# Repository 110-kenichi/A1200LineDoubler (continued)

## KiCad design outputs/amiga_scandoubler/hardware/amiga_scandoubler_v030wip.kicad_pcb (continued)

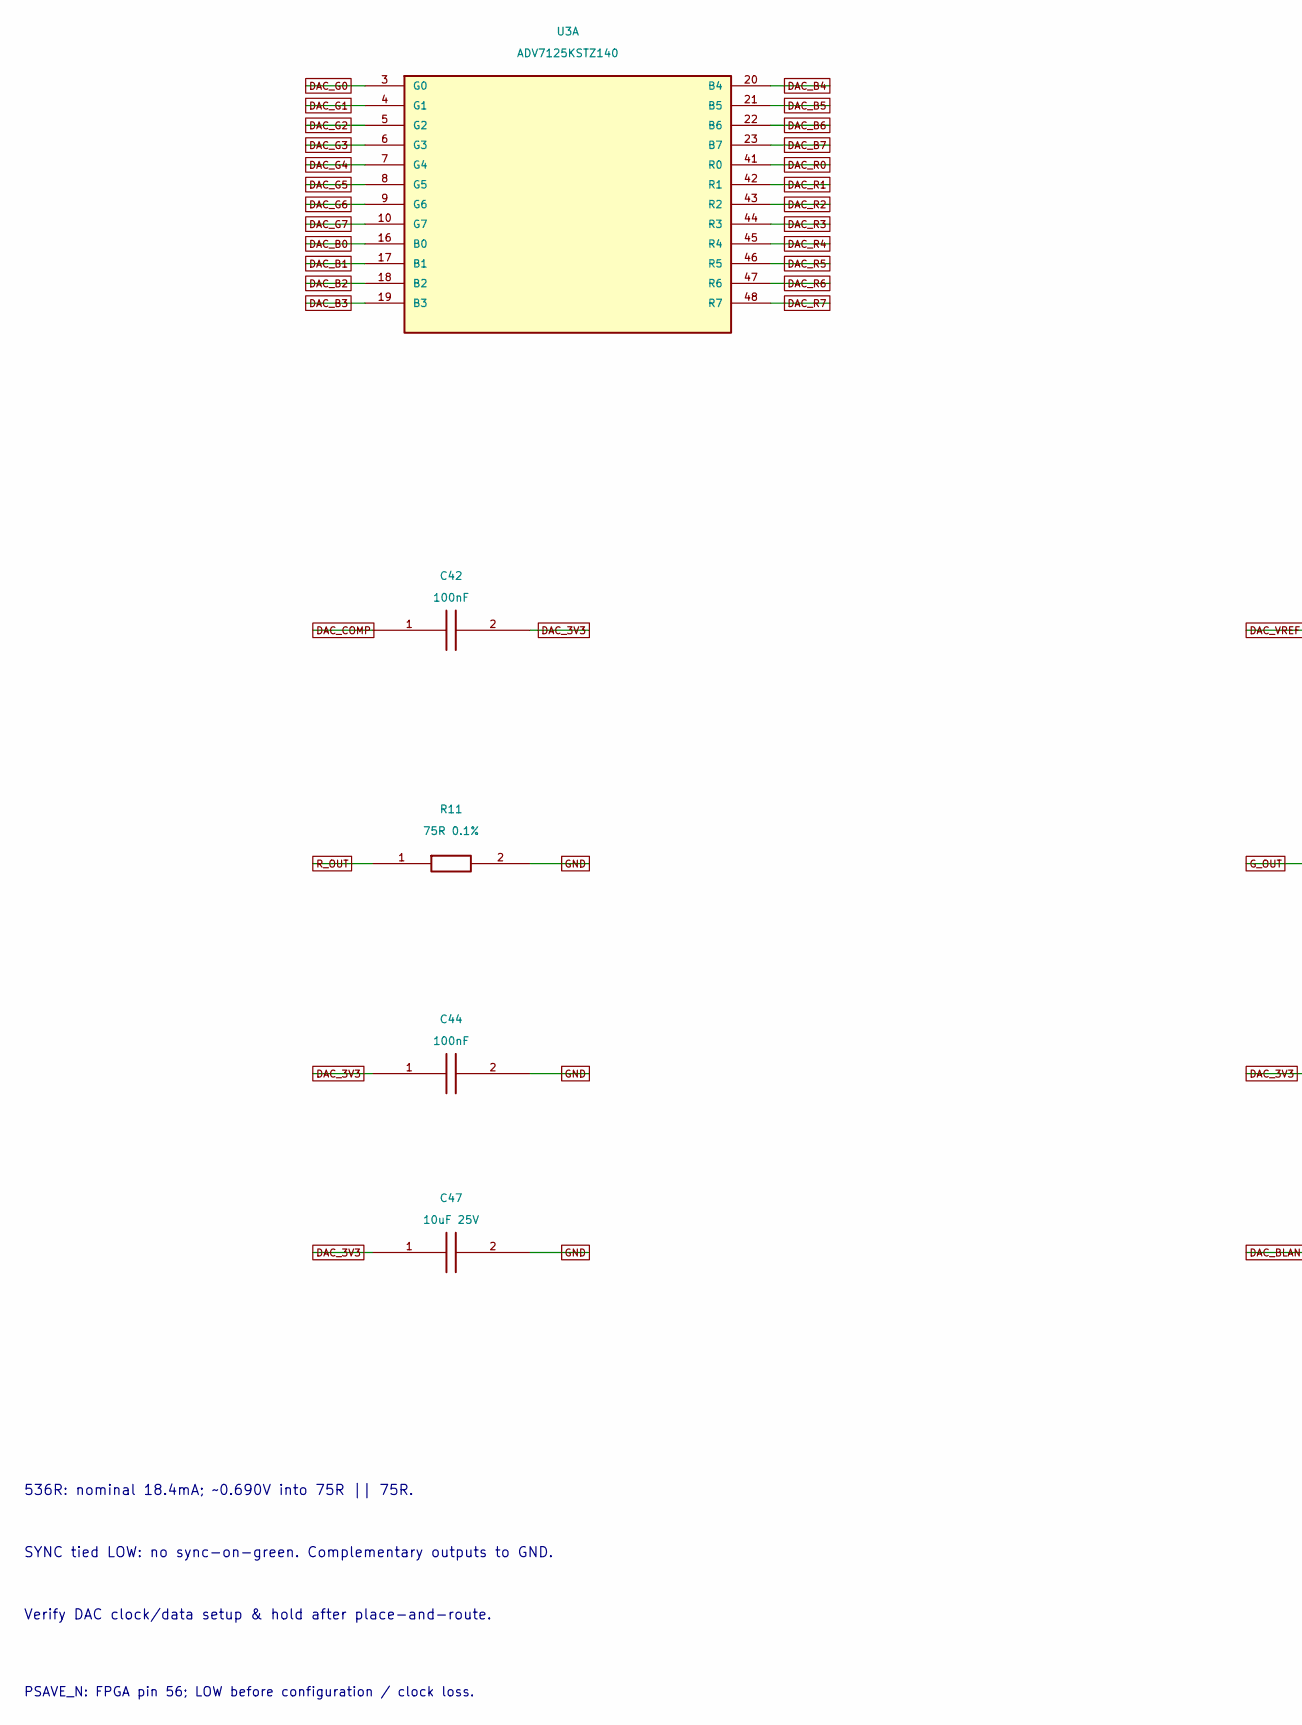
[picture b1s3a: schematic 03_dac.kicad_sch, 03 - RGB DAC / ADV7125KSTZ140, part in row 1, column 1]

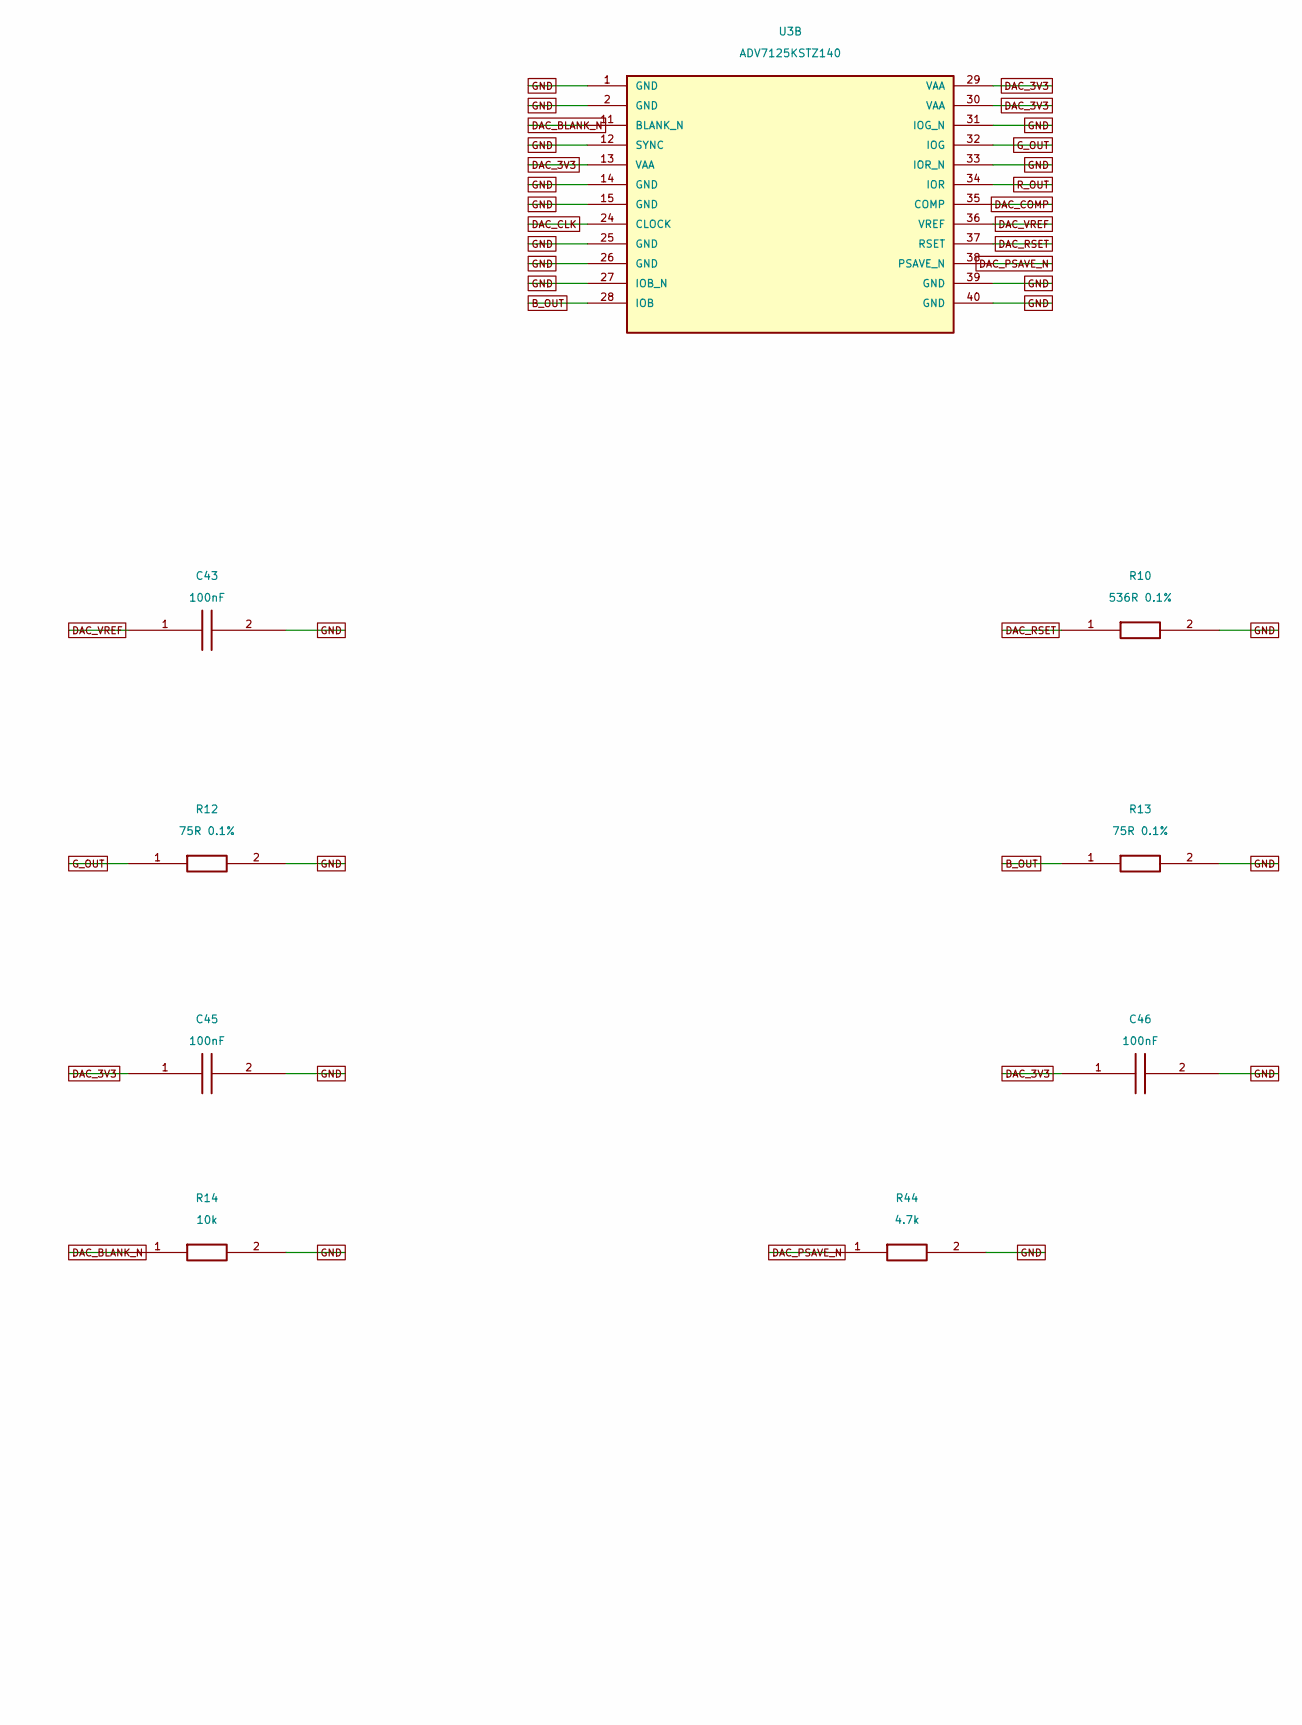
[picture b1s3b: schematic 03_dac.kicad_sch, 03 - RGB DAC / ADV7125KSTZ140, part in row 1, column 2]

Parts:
C42: 100nF; C_0402_1005Metric; MPN CL05B104KO5NNNC; LCSC C1525
C43, C44, C45, C46: 100nF; C_0603_1608Metric; MPN CC0603KRX7R9BB104; LCSC C14663
C47: 10uF 25V; C_0805_2012Metric; MPN CL21A106KAYNNNE; LCSC C15850
R10: 536R 0.1%; R_0603_1608Metric; MPN RT0603BRD07536RL; LCSC C861466
R11, R12, R13: 75R 0.1%; R_0603_1608Metric; MPN AR03BTCX0750; LCSC C319466
R14: 10k; R_0603_1608Metric; MPN 0603WAF1002T5E; LCSC C25804
R44: 4.7k; R_0603_1608Metric; MPN 0603WAF4701T5E; LCSC C23162
U3: ADV7125KSTZ140; LQFP-48_7x7mm_P0.5mm; MPN ADV7125KSTZ140; LCSC C9668

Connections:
B_OUT: R13.1, U3.28 (IOB); also elsewhere on the board
DAC_3V3: C42.2, C44.1, C45.1, C46.1, C47.1, U3.13 (VAA), U3.29 (VAA), U3.30 (VAA); also elsewhere on the board
DAC_B0: U3.16 (B0); also elsewhere on the board
DAC_B1: U3.17 (B1); also elsewhere on the board
DAC_B2: U3.18 (B2); also elsewhere on the board
DAC_B3: U3.19 (B3); also elsewhere on the board
DAC_B4: U3.20 (B4); also elsewhere on the board
DAC_B5: U3.21 (B5); also elsewhere on the board
DAC_B6: U3.22 (B6); also elsewhere on the board
DAC_B7: U3.23 (B7); also elsewhere on the board
DAC_BLANK_N: R14.1, U3.11 (BLANK_N); also elsewhere on the board
DAC_CLK: U3.24 (CLOCK); also elsewhere on the board
DAC_COMP: C42.1, U3.35 (COMP)
DAC_G0: U3.3 (G0); also elsewhere on the board
DAC_G1: U3.4 (G1); also elsewhere on the board
DAC_G2: U3.5 (G2); also elsewhere on the board
DAC_G3: U3.6 (G3); also elsewhere on the board
DAC_G4: U3.7 (G4); also elsewhere on the board
DAC_G5: U3.8 (G5); also elsewhere on the board
DAC_G6: U3.9 (G6); also elsewhere on the board
DAC_G7: U3.10 (G7); also elsewhere on the board
DAC_PSAVE_N: R44.1, U3.38 (PSAVE_N); also elsewhere on the board
DAC_R0: U3.41 (R0); also elsewhere on the board
DAC_R1: U3.42 (R1); also elsewhere on the board
DAC_R2: U3.43 (R2); also elsewhere on the board
DAC_R3: U3.44 (R3); also elsewhere on the board
DAC_R4: U3.45 (R4); also elsewhere on the board
DAC_R5: U3.46 (R5); also elsewhere on the board
DAC_R6: U3.47 (R6); also elsewhere on the board
DAC_R7: U3.48 (R7); also elsewhere on the board
DAC_RSET: R10.1, U3.37 (RSET)
DAC_VREF: C43.1, U3.36 (VREF)
GND: C43.2, C44.2, C45.2, C46.2, C47.2, R10.2, R11.2, R12.2, R13.2, R14.2, R44.2, U3.1 (GND), U3.2 (GND), U3.12 (SYNC), U3.14 (GND), U3.15 (GND), U3.25 (GND), U3.26 (GND), U3.27 (IOB_N), U3.31 (IOG_N), U3.33 (IOR_N), U3.39 (GND), U3.40 (GND); also elsewhere on the board
G_OUT: R12.1, U3.32 (IOG); also elsewhere on the board
R_OUT: R11.1, U3.34 (IOR); also elsewhere on the board

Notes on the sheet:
536R: nominal 18.4mA; ~0.690V into 75R || 75R.
SYNC tied LOW: no sync-on-green. Complementary outputs to GND.
Verify DAC clock/data setup & hold after place-and-route.
PSAVE_N: FPGA pin 56; LOW before configuration / clock loss.

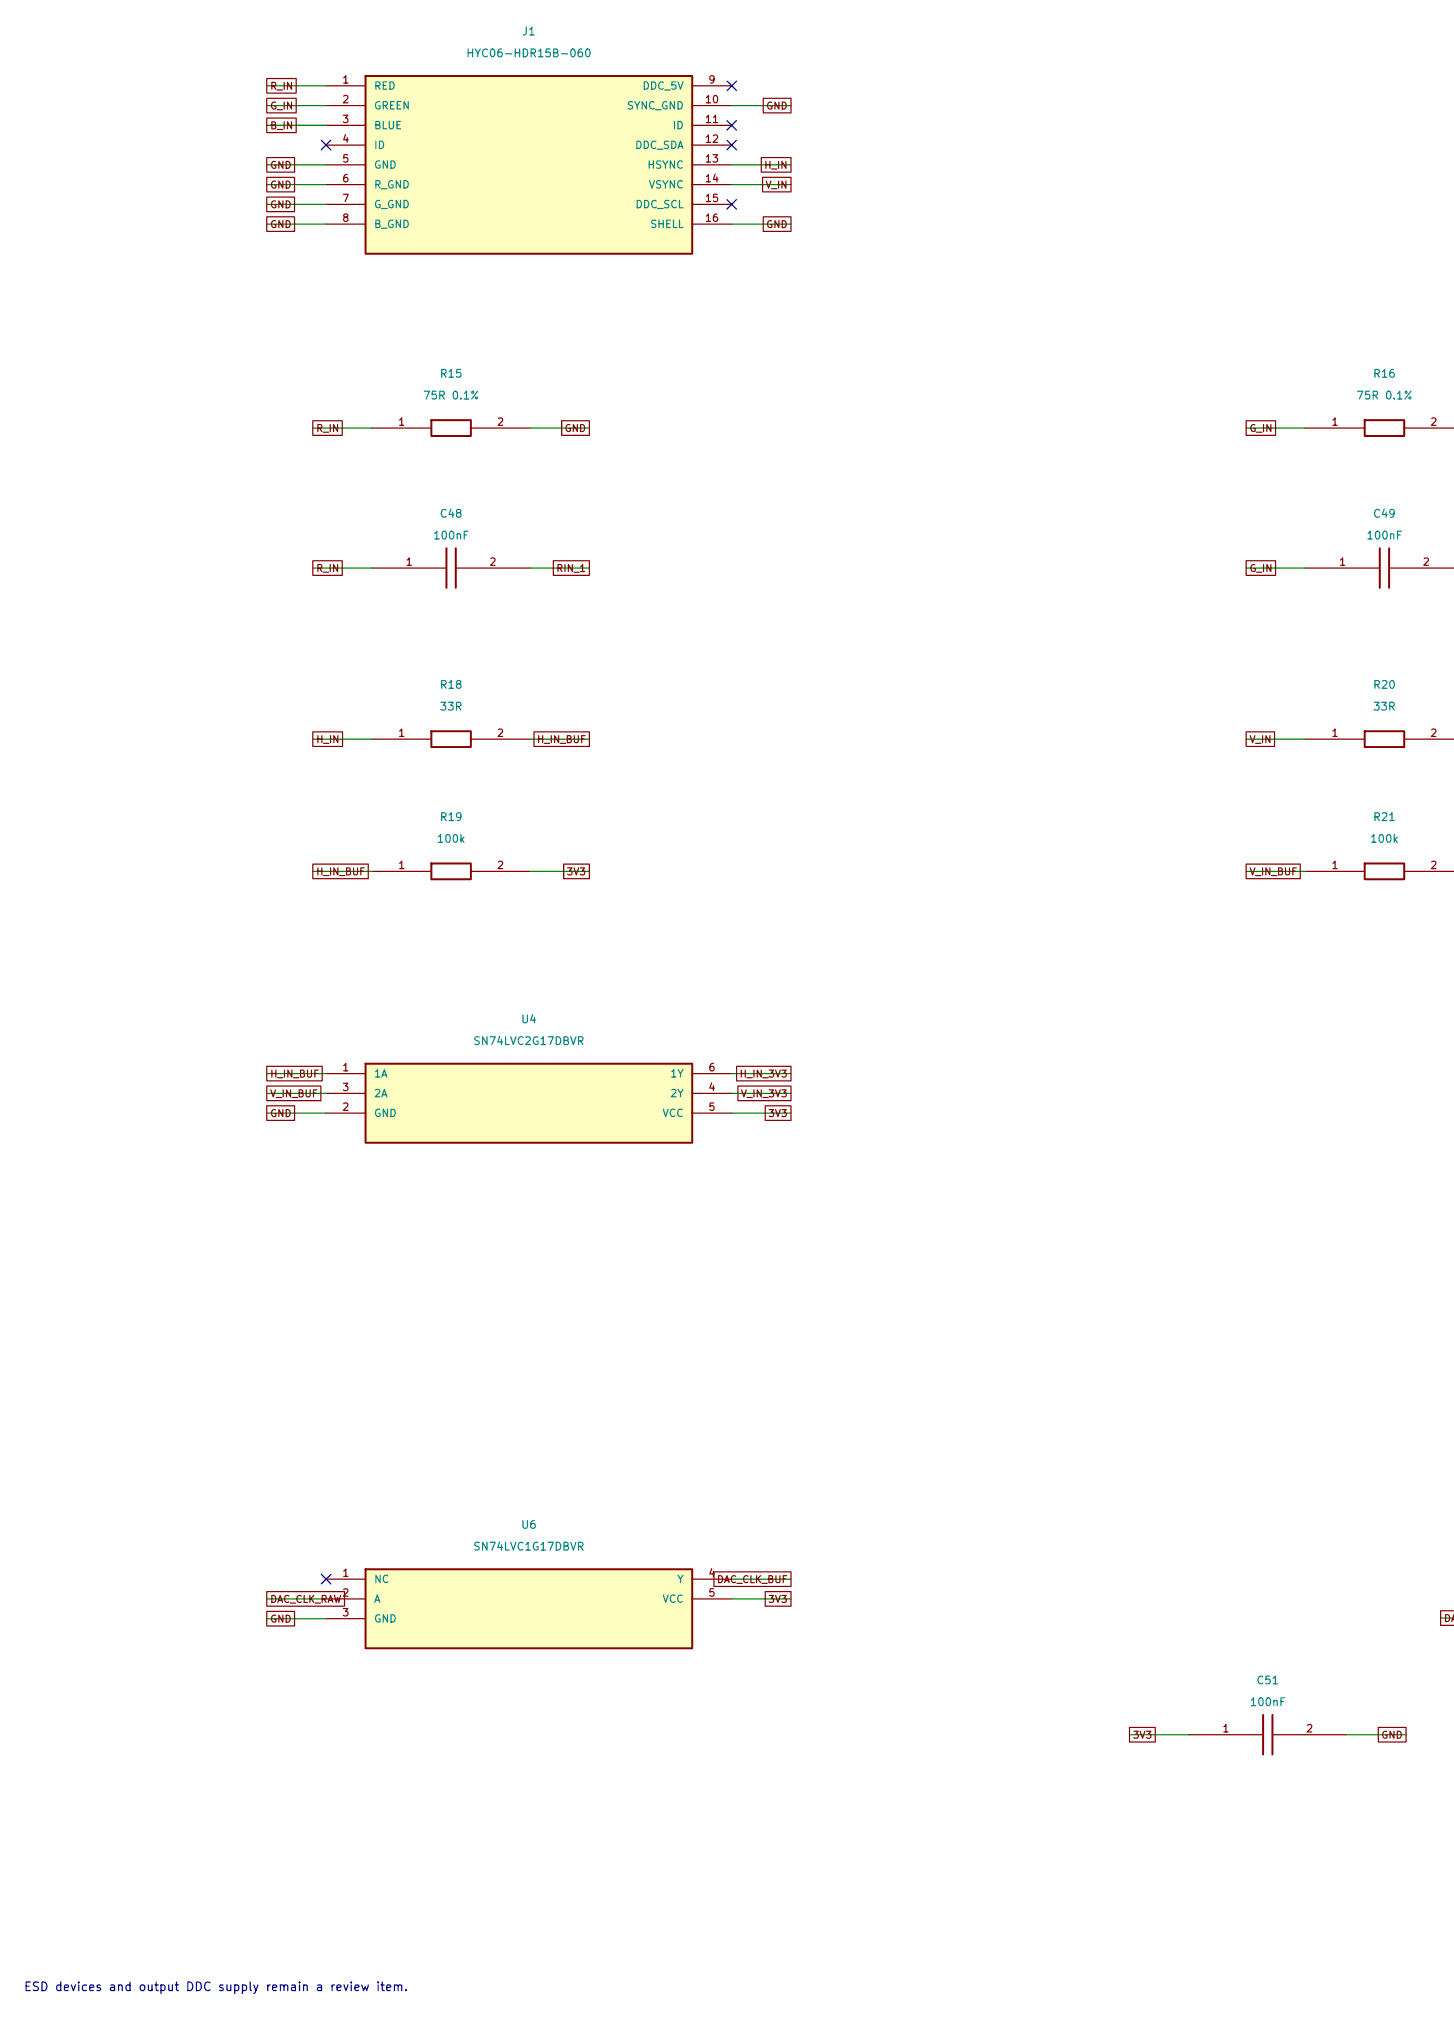
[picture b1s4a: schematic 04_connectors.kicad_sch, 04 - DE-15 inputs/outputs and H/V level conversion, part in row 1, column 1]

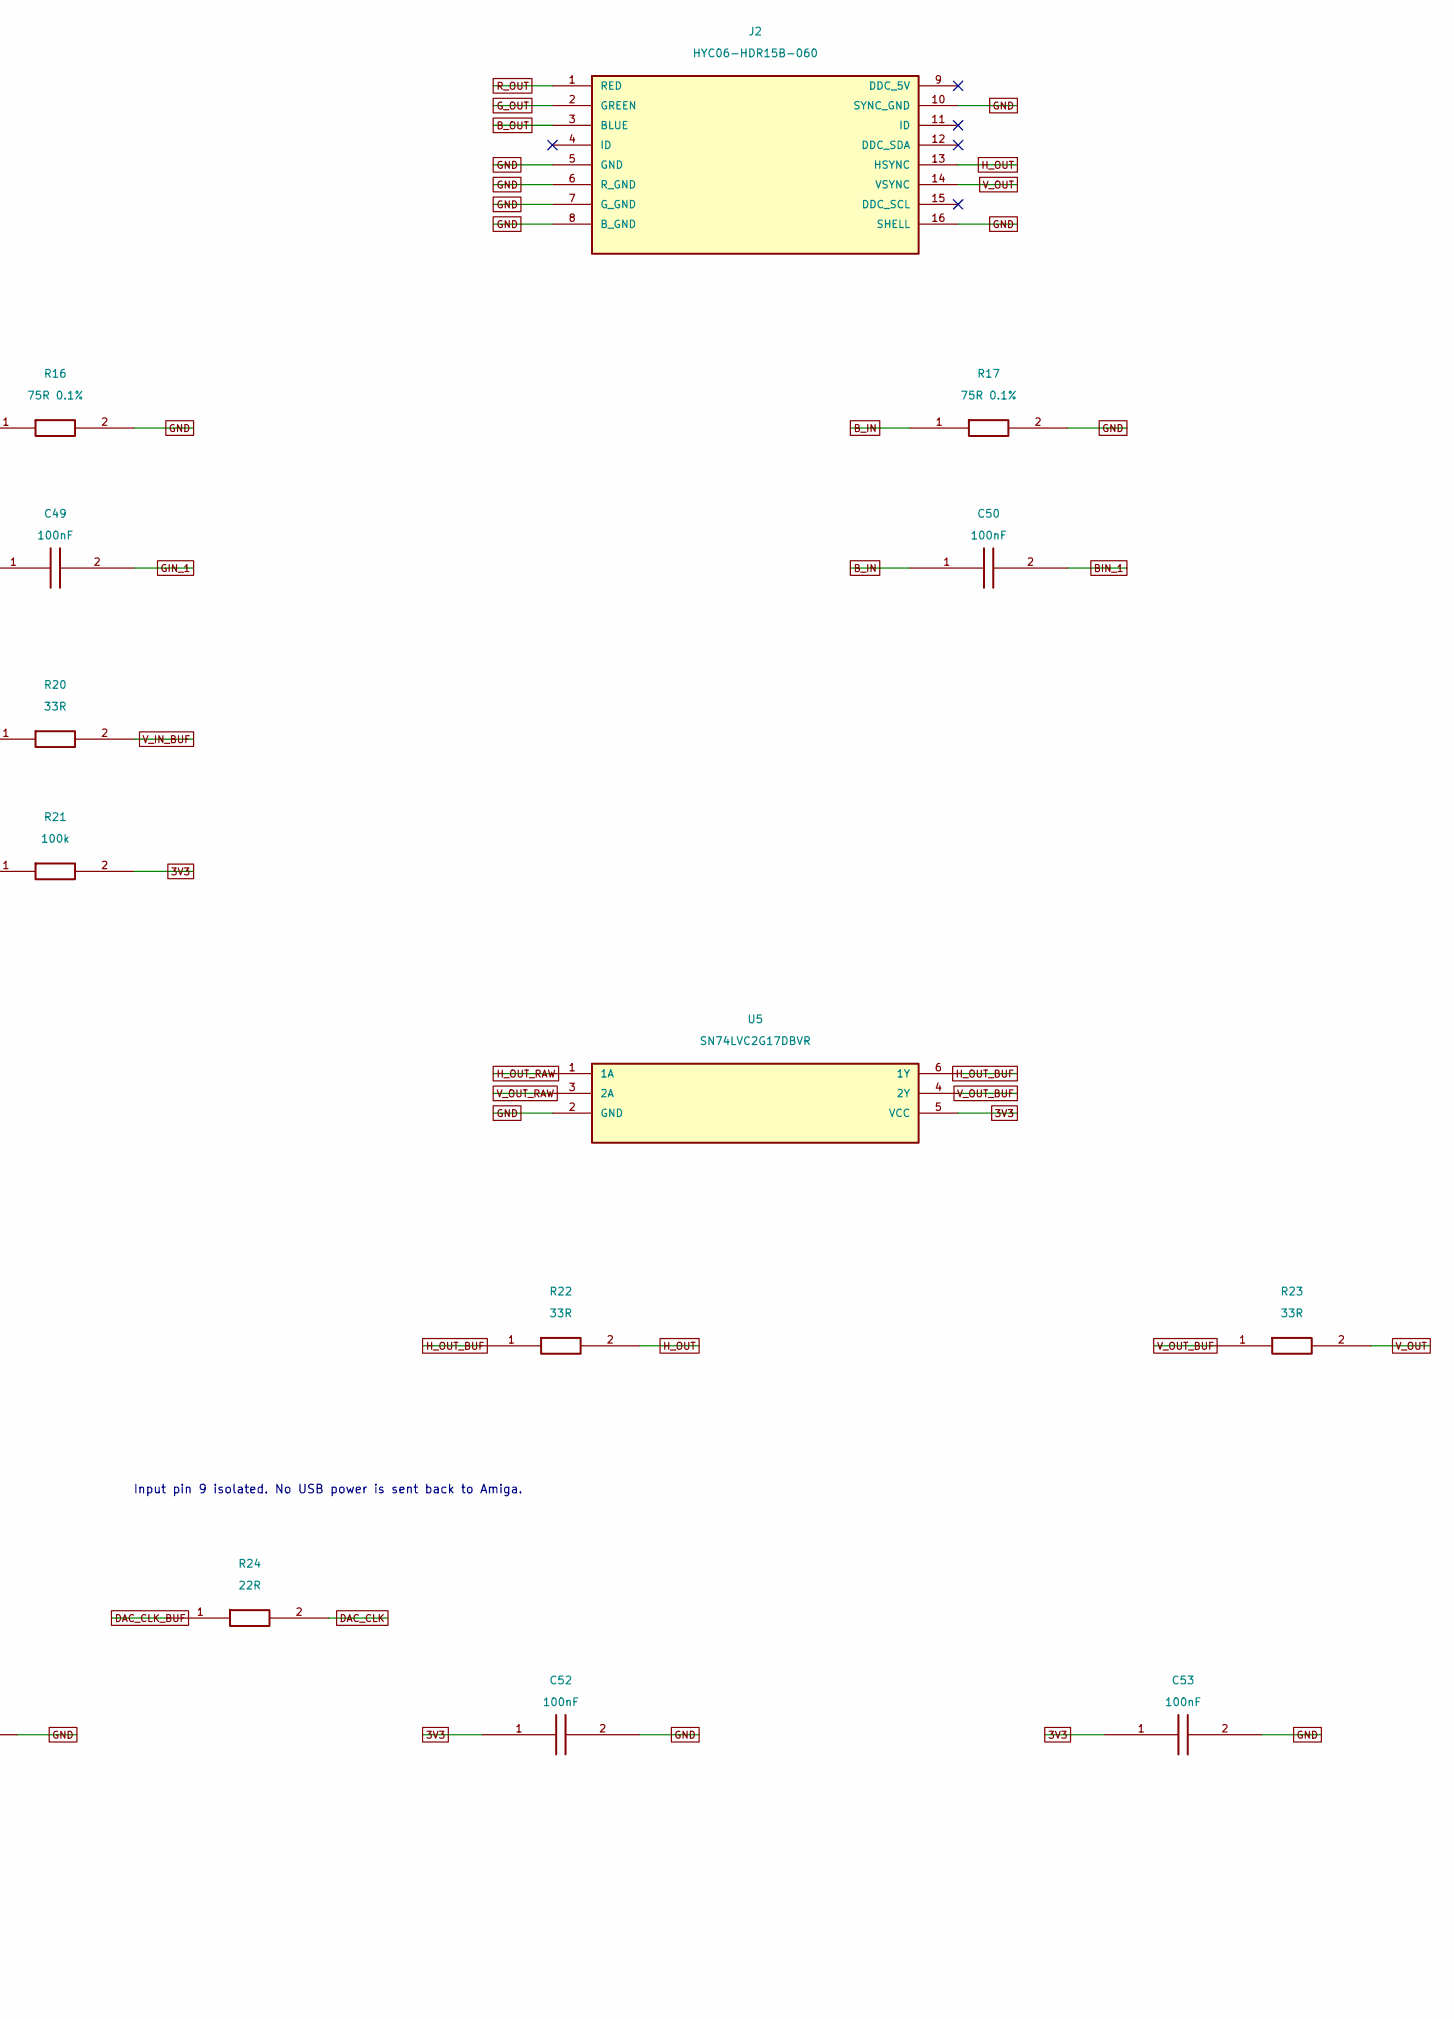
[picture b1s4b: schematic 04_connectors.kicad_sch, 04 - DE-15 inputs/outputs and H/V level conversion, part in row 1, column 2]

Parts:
C48, C49, C50, C51, C52, C53: 100nF; C_0603_1608Metric; MPN CC0603KRX7R9BB104; LCSC C14663
J1, J2: HYC06-HDR15B-060; DE15_HOAUC_HYC06-HDR15B-060; MPN HYC06-HDR15B-060; LCSC C711364
R15, R16, R17: 75R 0.1%; R_0603_1608Metric; MPN AR03BTCX0750; LCSC C319466
R18, R20, R22, R23: 33R; R_0603_1608Metric; MPN 0603WAF330JT5E; LCSC C23140
R19, R21: 100k; R_0603_1608Metric; MPN 0603WAF1003T5E; LCSC C25803
R24: 22R; R_0603_1608Metric; MPN 0603WAF220JT5E; LCSC C23345
U4, U5: SN74LVC2G17DBVR; SOT-23-6; MPN SN74LVC2G17DBVR; LCSC C19829674
U6: SN74LVC1G17DBVR; SOT-23-5; MPN SN74LVC1G17DBVR; LCSC C7836

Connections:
3V3: C51.1, C52.1, C53.1, R19.2, R21.2, U4.5 (VCC), U5.5 (VCC), U6.5 (VCC); also elsewhere on the board
BIN_1: C50.2; also elsewhere on the board
B_IN: C50.1, J1.3 (BLUE), R17.1
B_OUT: J2.3 (BLUE); also elsewhere on the board
DAC_CLK: R24.2; also elsewhere on the board
DAC_CLK_BUF: R24.1, U6.4 (Y)
DAC_CLK_RAW: U6.2 (A); also elsewhere on the board
GIN_1: C49.2; also elsewhere on the board
GND: C51.2, C52.2, C53.2, J1.5 (GND), J1.6 (R_GND), J1.7 (G_GND), J1.8 (B_GND), J1.10 (SYNC_GND), J1.16 (SHELL), J2.5 (GND), J2.6 (R_GND), J2.7 (G_GND), J2.8 (B_GND), J2.10 (SYNC_GND), J2.16 (SHELL), R15.2, R16.2, R17.2, U4.2 (GND), U5.2 (GND), U6.3 (GND); also elsewhere on the board
G_IN: C49.1, J1.2 (GREEN), R16.1
G_OUT: J2.2 (GREEN); also elsewhere on the board
H_IN: J1.13 (HSYNC), R18.1
H_IN_3V3: U4.6 (1Y); also elsewhere on the board
H_IN_BUF: R18.2, R19.1, U4.1 (1A)
H_OUT: J2.13 (HSYNC), R22.2
H_OUT_BUF: R22.1, U5.6 (1Y)
H_OUT_RAW: U5.1 (1A); also elsewhere on the board
RIN_1: C48.2; also elsewhere on the board
R_IN: C48.1, J1.1 (RED), R15.1
R_OUT: J2.1 (RED); also elsewhere on the board
V_IN: J1.14 (VSYNC), R20.1
V_IN_3V3: U4.4 (2Y); also elsewhere on the board
V_IN_BUF: R20.2, R21.1, U4.3 (2A)
V_OUT: J2.14 (VSYNC), R23.2
V_OUT_BUF: R23.1, U5.4 (2Y)
V_OUT_RAW: U5.3 (2A); also elsewhere on the board

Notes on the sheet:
Input pin 9 isolated. No USB power is sent back to Amiga.
ESD devices and output DDC supply remain a review item.

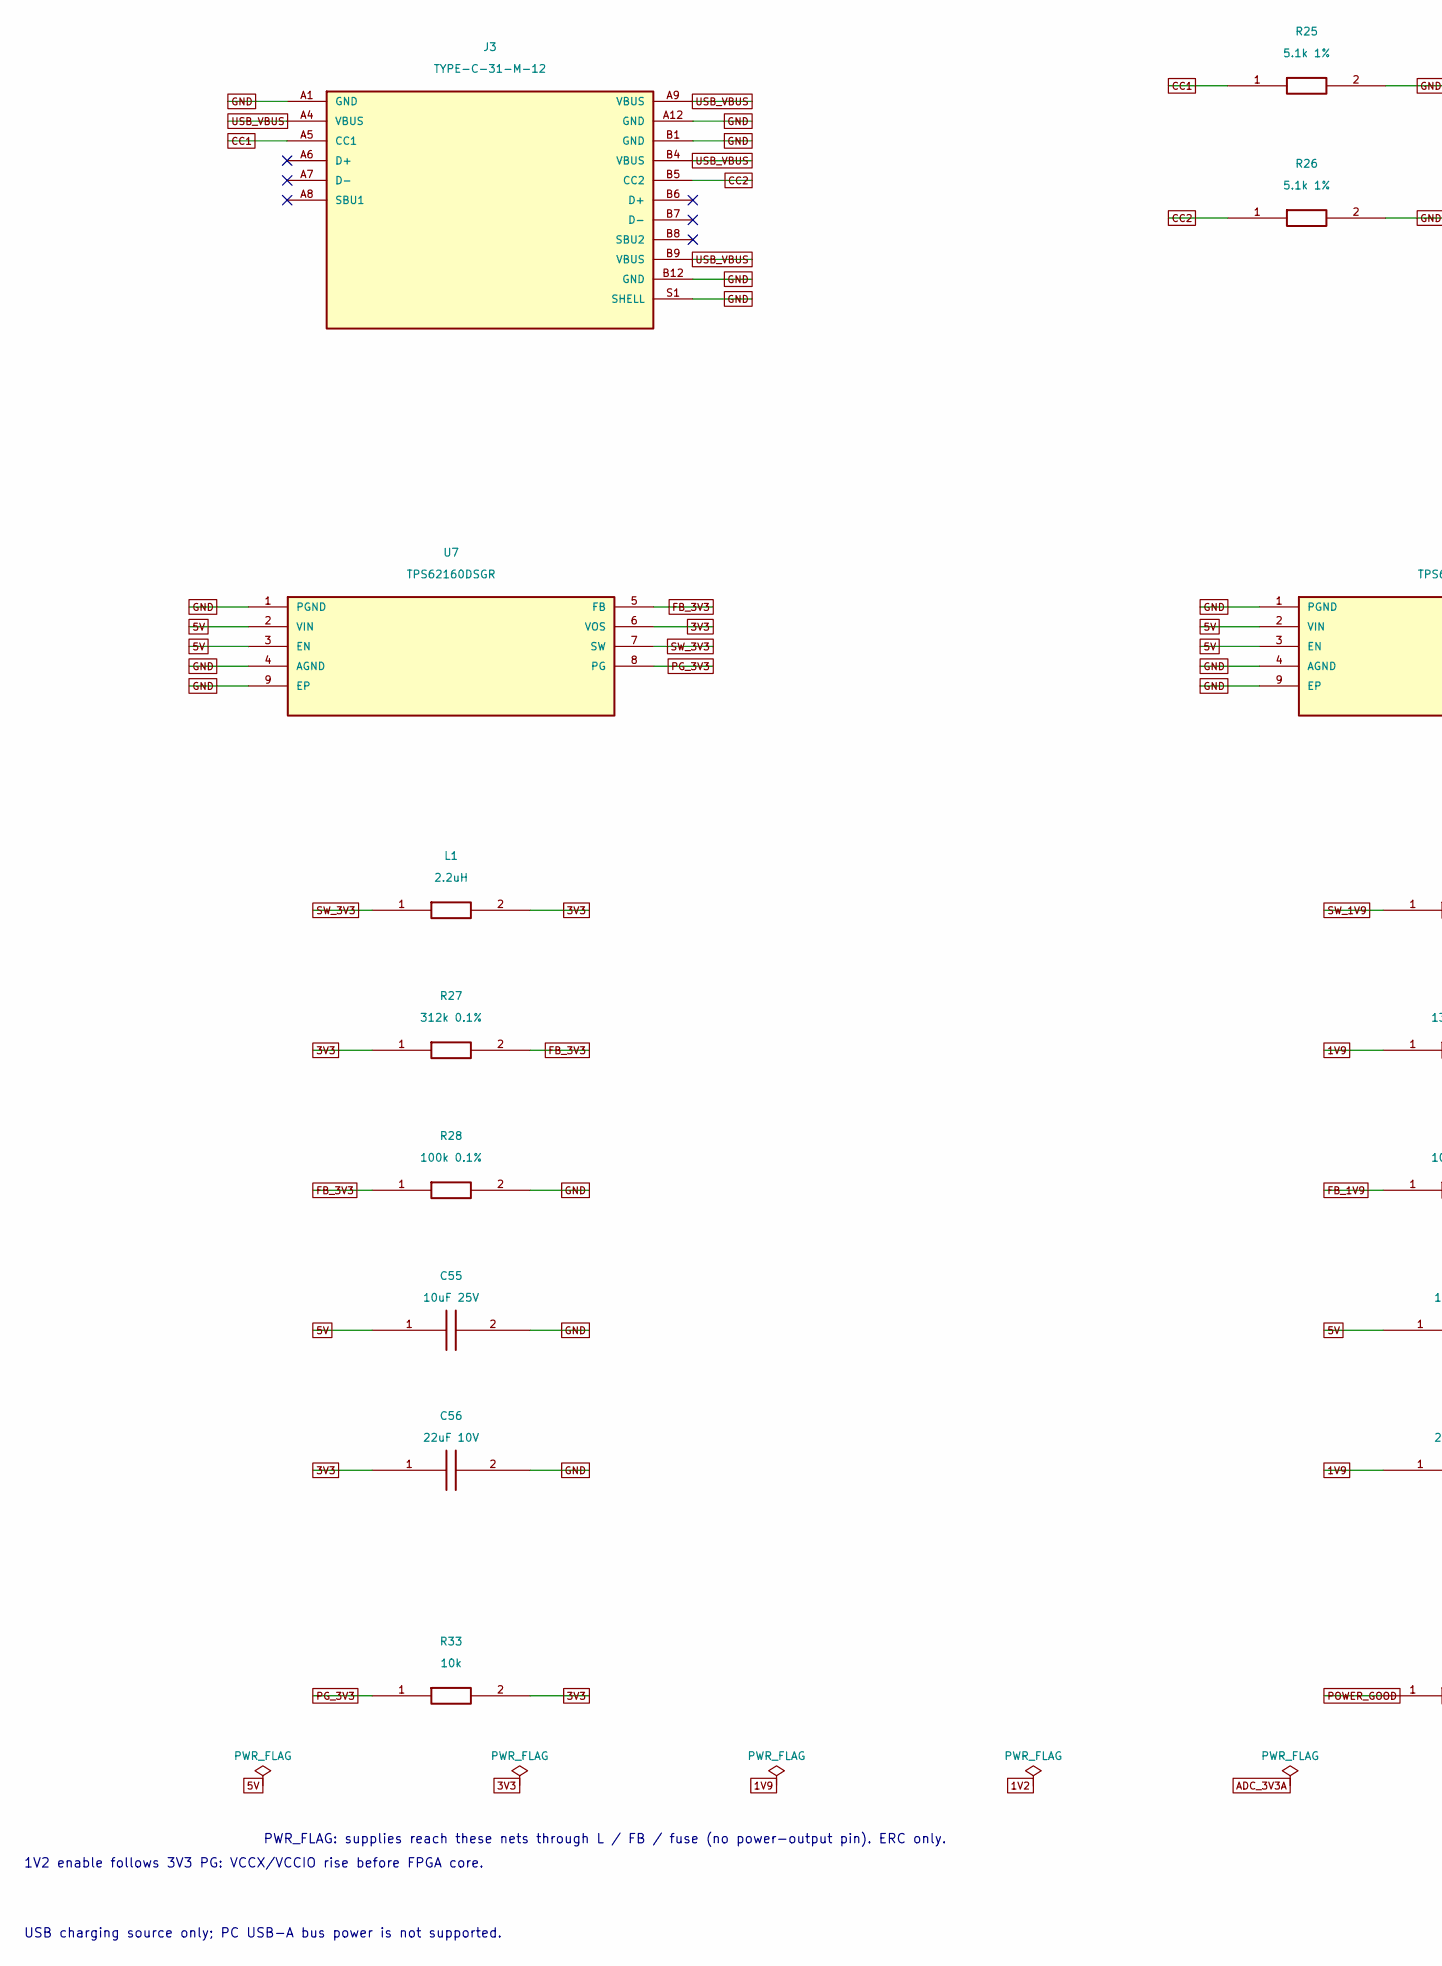
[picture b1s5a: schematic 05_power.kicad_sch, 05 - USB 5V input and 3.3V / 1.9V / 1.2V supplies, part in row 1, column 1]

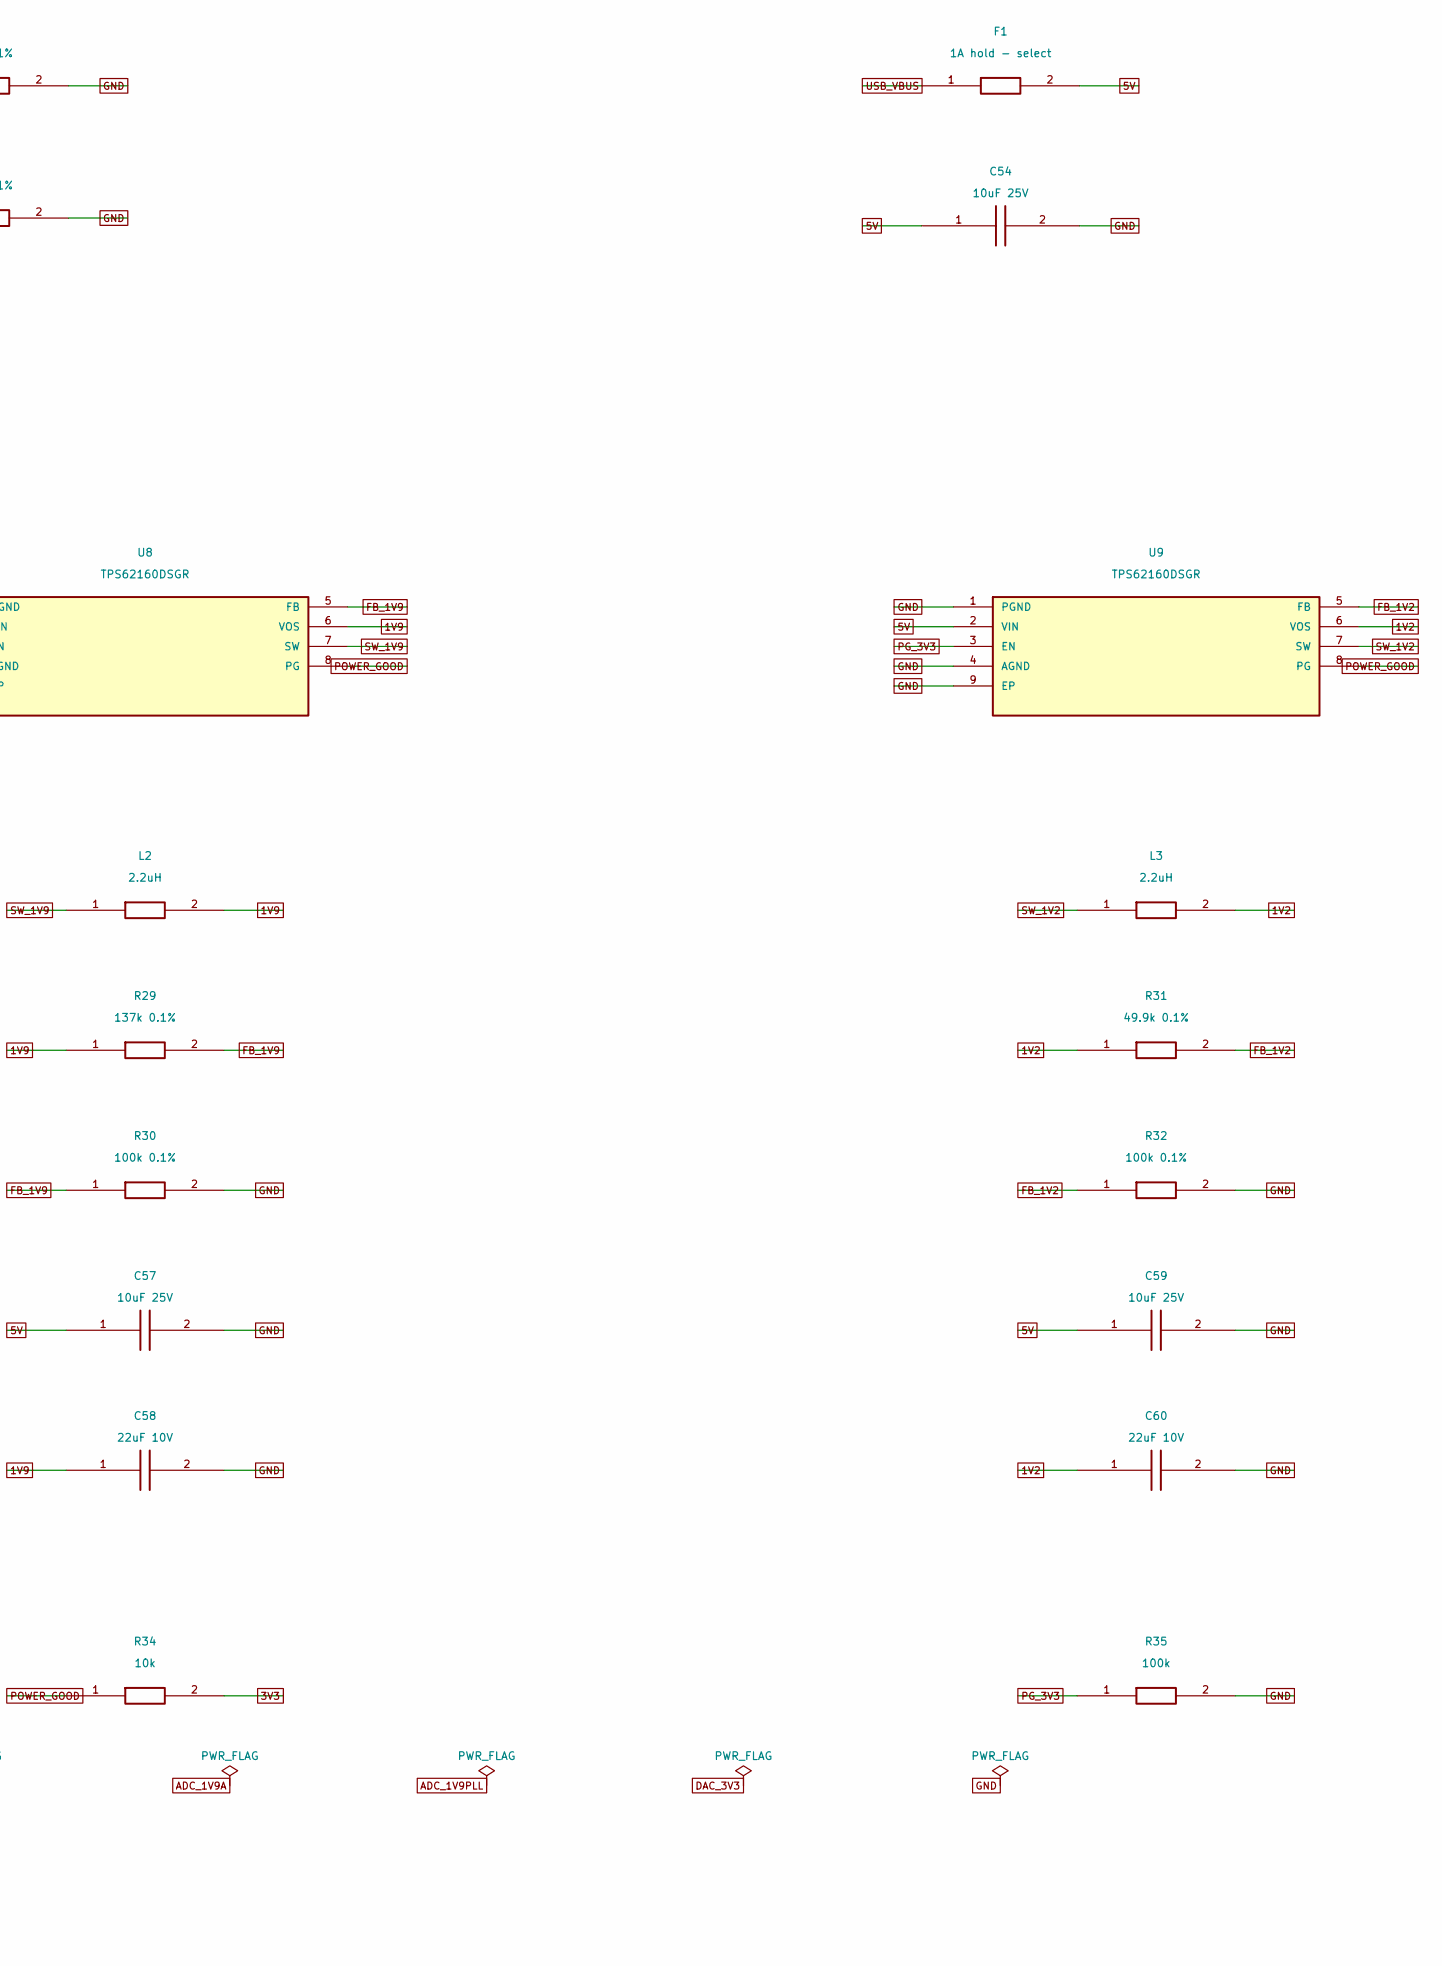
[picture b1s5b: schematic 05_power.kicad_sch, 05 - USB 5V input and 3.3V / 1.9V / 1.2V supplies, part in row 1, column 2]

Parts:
C54, C55, C57, C59: 10uF 25V; C_0805_2012Metric; MPN CL21A106KAYNNNE; LCSC C15850
C56, C58, C60: 22uF 10V; C_0805_2012Metric; MPN CL21A226MAQNNNE; LCSC C45783
F1: 1A hold - select; Fuse_1206_3216Metric; MPN SMD1206B110TFT; LCSC C269119
J3: TYPE-C-31-M-12; USB_C_Receptacle_HRO_TYPE-C-31-M-12_Slot0.8; MPN TYPE-C-31-M-12; LCSC C165948
L1, L2, L3: 2.2uH; L_TDK_VLS4012CX; MPN NRS4018T2R2MDGJ; LCSC C92959
R25, R26: 5.1k 1%; R_0603_1608Metric; MPN 0603WAF5101T5E; LCSC C23186
R27: 312k 0.1%; R_0603_1608Metric; MPN RT0603BRD07312KL; LCSC C861315
R28, R30, R32: 100k 0.1%; R_0603_1608Metric; MPN RT0603BRD07100KL; LCSC C122538
R29: 137k 0.1%; R_0603_1608Metric; MPN RT0603BRD07137KL; LCSC C861114
R31: 49.9k 0.1%; R_0603_1608Metric; MPN RT0603BRD0749K9L; LCSC C705780
R33, R34: 10k; R_0603_1608Metric; MPN 0603WAF1002T5E; LCSC C25804
R35: 100k; R_0603_1608Metric; MPN 0603WAF1003T5E; LCSC C25803
U7, U8, U9: TPS62160DSGR; WSON-8-1EP_2x2mm_P0.5mm_EP0.9x1.6mm; MPN TPS62160DSGR; LCSC C324077

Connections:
1V2: C60.1, L3.2, R31.1, U9.6 (VOS); also elsewhere on the board
1V9: C58.1, L2.2, R29.1, U8.6 (VOS); also elsewhere on the board
3V3: C56.1, L1.2, R27.1, R33.2, R34.2, U7.6 (VOS); also elsewhere on the board
5V: C54.1, C55.1, C57.1, C59.1, F1.2, U7.2 (VIN), U7.3 (EN), U8.2 (VIN), U8.3 (EN), U9.2 (VIN)
CC1: J3.A5 (CC1), R25.1
CC2: J3.B5 (CC2), R26.1
FB_1V2: R31.2, R32.1, U9.5 (FB)
FB_1V9: R29.2, R30.1, U8.5 (FB)
FB_3V3: R27.2, R28.1, U7.5 (FB)
GND: C54.2, C55.2, C56.2, C57.2, C58.2, C59.2, C60.2, J3.A1 (GND), J3.A12 (GND), J3.B1 (GND), J3.B12 (GND), J3.S1 (SHELL), R25.2, R26.2, R28.2, R30.2, R32.2, R35.2, U7.1 (PGND), U7.4 (AGND), U7.9 (EP), U8.1 (PGND), U8.4 (AGND), U8.9 (EP), U9.1 (PGND), U9.4 (AGND), U9.9 (EP); also elsewhere on the board
PG_3V3: R33.1, R35.1, U7.8 (PG), U9.3 (EN)
POWER_GOOD: R34.1, U8.8 (PG), U9.8 (PG); also elsewhere on the board
SW_1V2: L3.1, U9.7 (SW)
SW_1V9: L2.1, U8.7 (SW)
SW_3V3: L1.1, U7.7 (SW)
USB_VBUS: F1.1, J3.A4 (VBUS), J3.A9 (VBUS), J3.B4 (VBUS), J3.B9 (VBUS)

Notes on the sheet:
1V2 enable follows 3V3 PG: VCCX/VCCIO rise before FPGA core.
USB charging source only; PC USB-A bus power is not supported.
PWR_FLAG: supplies reach these nets through L / FB / fuse (no power-output pin). ERC only.
